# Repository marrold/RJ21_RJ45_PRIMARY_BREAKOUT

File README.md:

# RJ21_RJ45_PRIMARY_BREAKOUT

A breakout board which converts an RJ21 connector into multiple RJ45s - 12 lines, and 4 additional RJ45s carrying 4 lines each to be broken out on additional secondary boards.

The slot allows you to secure the RJ21 with velcro or a cable tie.

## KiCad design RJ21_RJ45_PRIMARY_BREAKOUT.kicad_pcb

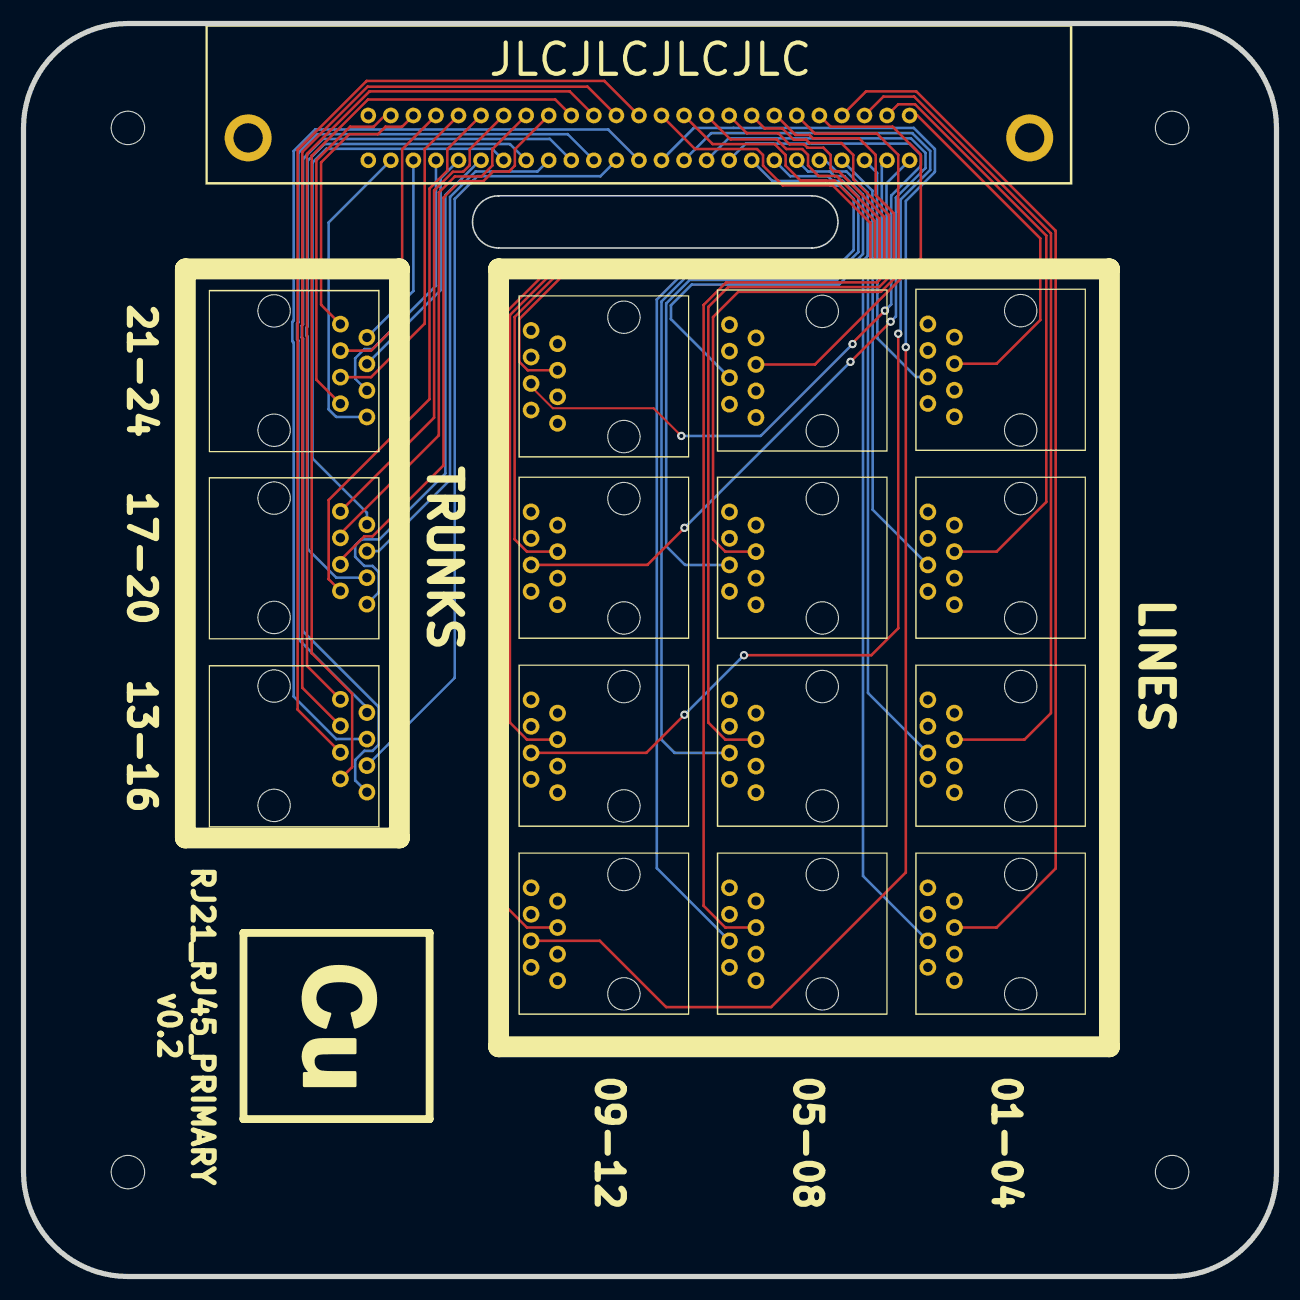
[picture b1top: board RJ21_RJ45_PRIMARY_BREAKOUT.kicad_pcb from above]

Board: 2 copper layers, 120.0 x 120.0 mm, 16 parts (0 on the bottom side), 48 nets.

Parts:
J1, J2, J3, J4, J5, J6, J7, J8, J9, J10, J11, J12, J13, J14, J15: RJ45; AliExpress_Horizontal_RJ45
J17: RJ21 Connector; AliExpress_RJ21

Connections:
/L1+: J1.5, J17.26
/L1-: J1.4, J17.1
/L2+: J2.5, J17.27
/L2-: J2.4, J17.2
/L3+: J3.5, J17.28
/L3-: J3.4, J17.3
/L4+: J4.5, J17.29
/L4-: J4.4, J17.4
/L5+: J5.5, J17.30
/L5-: J5.4, J17.5
/L6+: J6.5, J17.31
/L6-: J6.4, J17.6
/L7+: J7.5, J17.32
/L7-: J7.4, J17.7
/L8+: J8.5, J17.33
/L8-: J8.4, J17.8
/L9+: J9.5, J17.34
/L9-: J9.4, J17.9
/L10+: J10.5, J17.35
/L10-: J10.4, J17.10
/L11+: J11.5, J17.36
/L11-: J11.4, J17.11
/L12+: J12.5, J17.37
/L12-: J12.4, J17.12
/L13+: J13.5, J17.38
/L13-: J13.4, J17.13
/L14+: J13.3, J17.39
/L14-: J13.6, J17.14
/L15+: J13.1, J17.40
/L15-: J13.2, J17.15
/L16+: J13.7, J17.41
/L16-: J13.8, J17.16
/L17+: J14.5, J17.42
/L17-: J14.4, J17.17
/L18+: J14.3, J17.43
/L18-: J14.6, J17.18
/L19+: J14.1, J17.44
/L19-: J14.2, J17.19
/L20+: J14.7, J17.45
/L20-: J14.8, J17.20
/L21+: J15.5, J17.46
/L21-: J15.4, J17.21
/L22+: J15.3, J17.47
/L22-: J15.6, J17.22
/L23+: J15.1, J17.48
/L23-: J15.2, J17.23
/L24+: J15.7, J17.49
/L24-: J15.8, J17.24

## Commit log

2022-02-09 Add note about additional RJ45 to README
2022-02-09 Add footprints
2022-02-09 Add gerbers
2022-02-09 Rename edge cuts file to gko
2022-02-09 Update PCB and gerbers to sync changes
2022-11-27 Fix silk screen, re-align J3, remove J16
2022-11-27 Update gerbers
2024-01-05 Update silkscreen
2024-04-13 Regenerate Gerbers
